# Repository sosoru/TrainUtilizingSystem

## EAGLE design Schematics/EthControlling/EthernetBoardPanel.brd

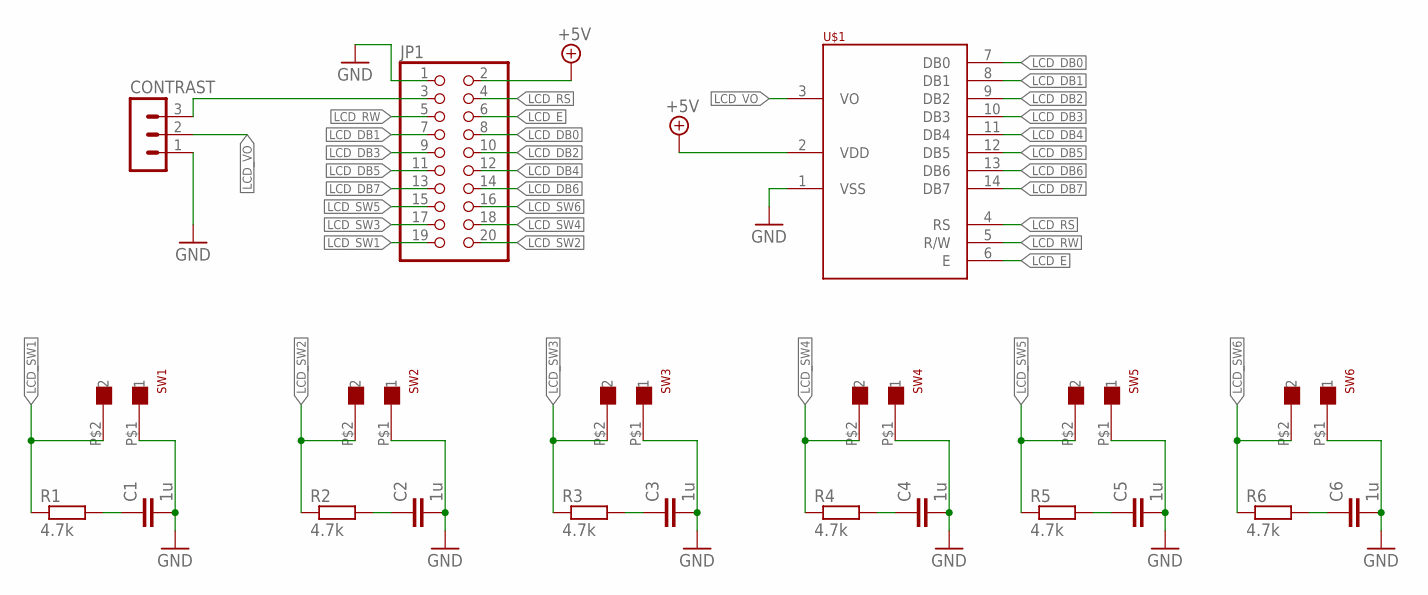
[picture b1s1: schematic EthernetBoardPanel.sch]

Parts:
C1, C2, C3, C4, C5, C6: 1u; C025-025X050
CONTRAST: MA03-1
JP1: PINHD-2X10; 2X10
R1, R2, R3, R4, R5, R6: 4.7k; 0204/7
SW1, SW2, SW3, SW4, SW5, SW6: XH-2
U$1: SC2004

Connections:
+5V: JP1.2, U$1.2 (VDD)
GND: C1.2, C2.2, C3.2, C4.2, C5.2, C6.2, CONTRAST.1, JP1.1, SW1.P$1 (1), SW2.P$1 (1), SW3.P$1 (1), SW4.P$1 (1), SW5.P$1 (1), SW6.P$1 (1), U$1.1 (VSS)
LCD_DB0: JP1.8, U$1.7 (DB0)
LCD_DB1: JP1.7, U$1.8 (DB1)
LCD_DB2: JP1.10, U$1.9 (DB2)
LCD_DB3: JP1.9, U$1.10 (DB3)
LCD_DB4: JP1.12, U$1.11 (DB4)
LCD_DB5: JP1.11, U$1.12 (DB5)
LCD_DB6: JP1.14, U$1.13 (DB6)
LCD_DB7: JP1.13, U$1.14 (DB7)
LCD_E: JP1.6, U$1.6 (E)
LCD_RS: JP1.4, U$1.4 (RS)
LCD_RW: JP1.5, U$1.5 (R/W)
LCD_SW1: JP1.19, R1.1, SW1.P$2 (2)
LCD_SW2: JP1.20, R2.1, SW2.P$2 (2)
LCD_SW3: JP1.17, R3.1, SW3.P$2 (2)
LCD_SW4: JP1.18, R4.1, SW4.P$2 (2)
LCD_SW5: JP1.15, R5.1, SW5.P$2 (2)
LCD_SW6: JP1.16, R6.1, SW6.P$2 (2)
LCD_VO: CONTRAST.2, U$1.3 (VO)
unnamed: CONTRAST.3, JP1.3
unnamed: C5.1, R5.2
unnamed: C2.1, R2.2
unnamed: C3.1, R3.2
unnamed: C4.1, R4.2
unnamed: C1.1, R1.2
unnamed: C6.1, R6.2

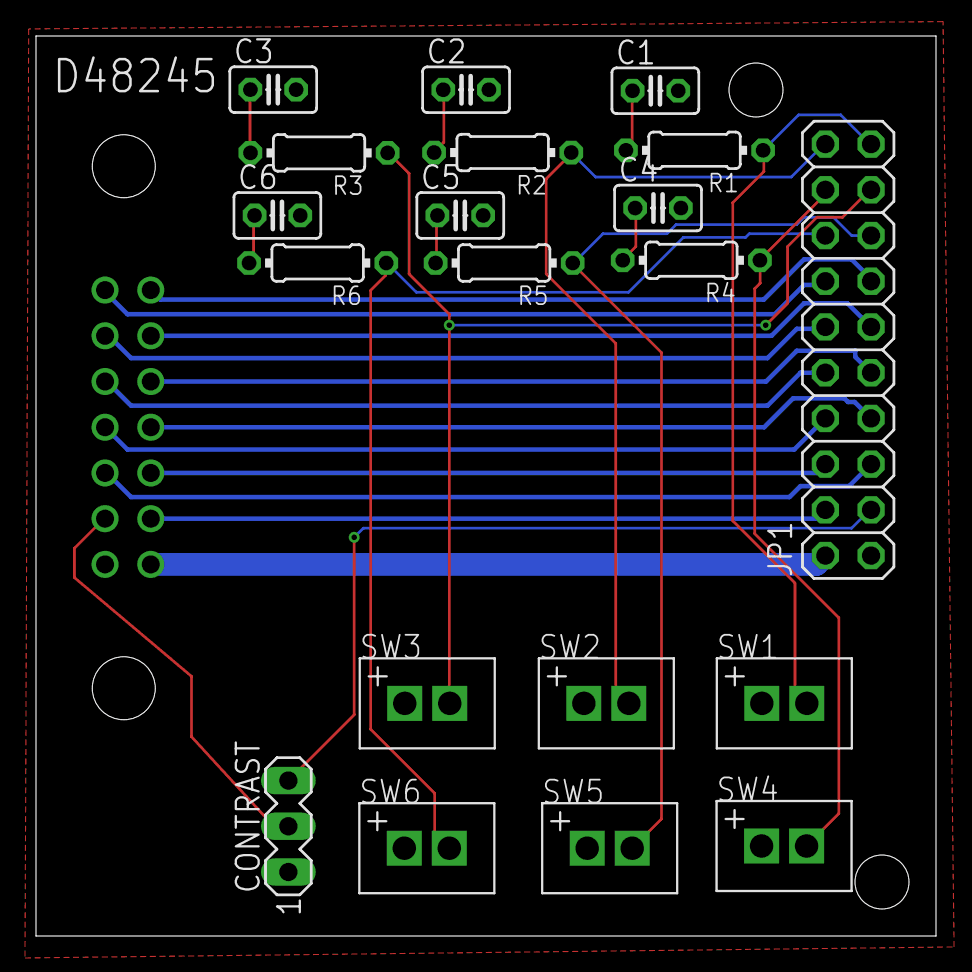
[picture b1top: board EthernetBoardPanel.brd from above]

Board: 2 copper layers, 50.0 x 50.0 mm, 21 parts (1 on the bottom side), 27 nets.

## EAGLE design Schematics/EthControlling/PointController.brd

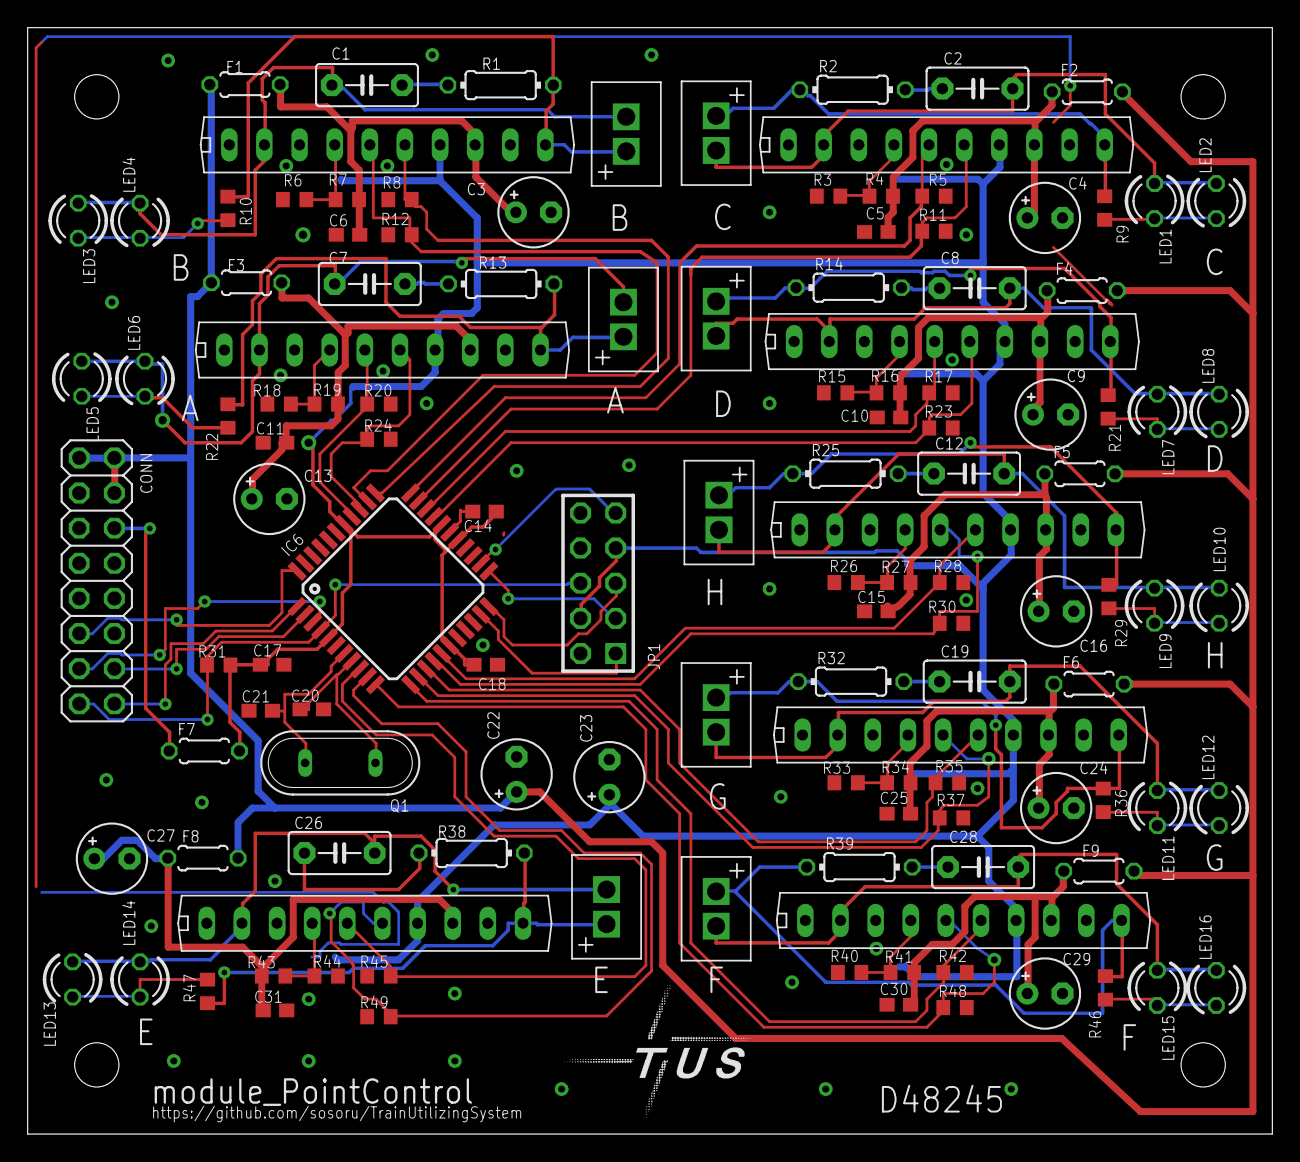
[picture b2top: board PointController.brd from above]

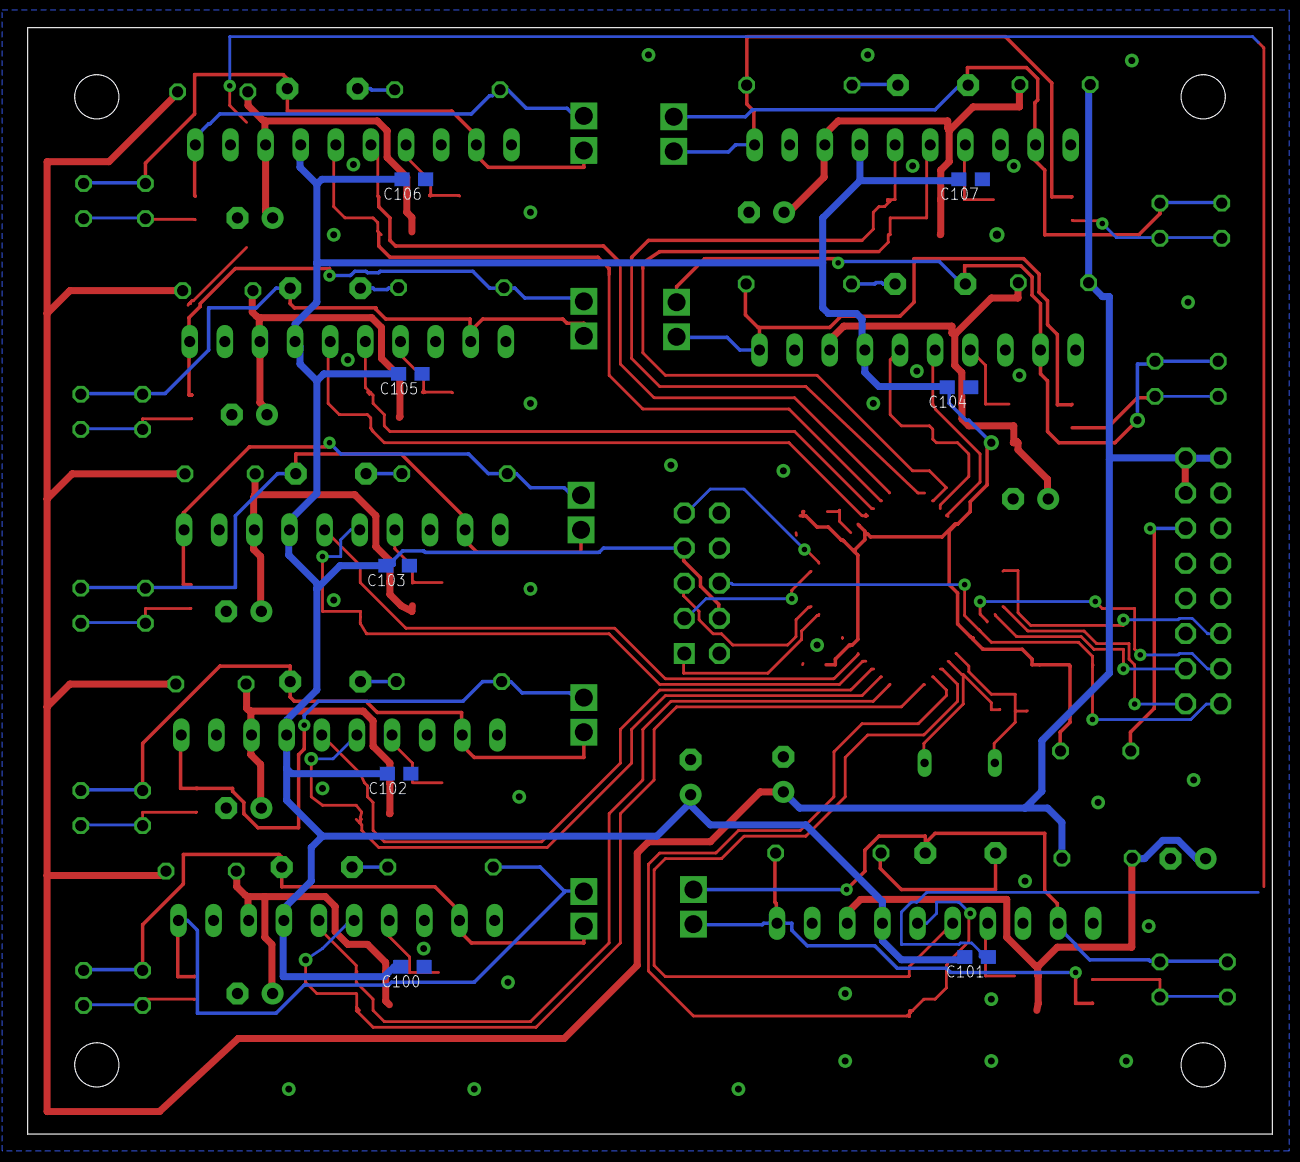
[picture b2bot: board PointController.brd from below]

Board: 2 copper layers, 90.0 x 80.0 mm, 133 parts (8 on the bottom side), 79 nets.

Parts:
A: XH-2
B: XH-2
C: XH-2
C1, C2, C7, C8, C12, C19, C26, C28: 47u; C5B3
C3, C4, C9, C13, C16, C24, C27, C29: E2,5-5
C5, C6, C10, C11, C14, C15, C17, C18, C25, C30, C31, C100, C101, C102, C103, C104, C105, C106, C107: 0.1u; C1608
C20, C21: 22p; C1608
C22, C23: 47u; E2,5-5
CONN: TUS_MODULE_SUPPLY; 2X08
D: XH-2
E: XH-2
F: XH-2
F1, F2, F3, F4, F5, F6, F7, F8, F9: POLYSWITCH_20204/5; 0204/5
G: XH-2
H: XH-2
IC1, IC2, IC3, IC4, IC5, IC7, IC8, IC9: TA7291; HSIP10
IC6: MEGA164P/324P/644P-AU; TQFP44
JP1: AVR-JTAG-10
LED1, LED3, LED5, LED7, LED9, LED11, LED13, LED15: G; LED3MM
LED2, LED4, LED6, LED8, LED10, LED12, LED14, LED16: O; LED3MM
Q1: 20.000M; QS
R1, R2, R13, R14, R25, R32, R38, R39: 10k; 0204/7
R3, R5, R6, R8, R11, R12, R15, R17, R18, R20, R23, R24, R26, R28, R30, R33, R35, R37, R40, R42, R44, R45, R48, R49: 100k; R0603
R4, R7, R16, R19, R27, R31, R34, R41, R43: 10k; R0603
R9, R10, R21, R22, R29, R36, R46, R47: 1k; R0603

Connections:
5V: C14.1, C17.1, C18.1, C23.+, C100.2, C101.2, C102.2, C103.2, C104.2, C105.2, C106.2, C107.2, F7.2, IC1.7, IC2.7, IC3.7, IC4.7, IC5.7, IC6.5, IC6.17, IC6.27, IC6.29, IC6.38, IC7.7, IC8.7, IC9.7, JP1.4, JP1.7, R31.1
!RESET: CONN.15, IC6.4, JP1.6, R31.2
!SS: CONN.11, IC6.44
+12V: C22.+, CONN.1, CONN.2, CONN.4, F1.2, F2.2, F3.2, F4.2, F5.2, F6.2, F8.2, F9.2
GND: C3.-, C4.-, C5.1, C6.1, C9.-, C10.1, C11.1, C13.-, C14.2, C15.1, C16.-, C17.2, C18.2, C20.1, C21.1, C22.-, C23.-, C24.-, C25.1, C27.-, C29.-, C30.1, C31.1, C100.1, C101.1, C102.1, C103.1, C104.1, C105.1, C106.1, C107.1, CONN.3, CONN.5, CONN.7, CONN.8, CONN.9, CONN.12, IC1.1, IC2.1, IC3.1, IC4.1, IC5.1, IC6.6, IC6.18, IC6.28, IC6.39, IC7.1, IC8.1, IC9.1, JP1.2, JP1.10, R3.2, R5.1, R6.2, R8.1, R11.1, R12.1, R15.2, R17.1, R18.2, R20.1, R23.1, R24.1, R26.2, R28.1, R30.1, R33.2, R35.1, R37.1, R40.2, R42.1, R44.2, R45.1, R48.1, R49.1
MISO: CONN.14, IC6.2
MOSI: CONN.16, IC6.1
unnamed: LED5.K, LED6.A, R22.2
unnamed: IC1.4, R6.1, R7.1
unnamed: C20.2, IC6.8, Q1.1
unnamed: C21.2, IC6.7, Q1.2
unnamed: B.P$2, C1.2, IC1.2, LED3.A, LED4.K
unnamed: IC4.4, R18.1, R19.1
unnamed: A.P$2, C7.2, IC4.2, LED5.A, LED6.K
unnamed: A.P$1, IC4.10, R13.1, R22.1
unnamed: C7.1, R13.2
unnamed: B.P$1, IC1.10, R1.1, R10.1
unnamed: C1.1, R1.2
unnamed: LED3.K, LED4.A, R10.2
unnamed: IC2.4, R3.1, R4.1
unnamed: C.P$2, C2.2, IC2.2, LED1.A, LED2.K
unnamed: C.P$1, IC2.10, R2.1, R9.1
unnamed: C2.1, R2.2
unnamed: LED1.K, LED2.A, R9.2
unnamed: IC3.4, R15.1, R16.1
unnamed: C8.2, D.P$2, IC3.2, LED7.A, LED8.K
unnamed: D.P$1, IC3.10, R14.1, R21.1
unnamed: C8.1, R14.2
unnamed: LED7.K, LED8.A, R21.2
unnamed: IC9.4, R43.1, R44.1
unnamed: C26.2, E.P$2, IC9.2, LED13.A, LED14.K
unnamed: E.P$1, IC9.10, R38.1, R47.1
unnamed: C26.1, R38.2
unnamed: LED13.K, LED14.A, R47.2
unnamed: IC8.4, R40.1, R41.1
unnamed: C28.2, F.P$2, IC8.2, LED15.A, LED16.K
unnamed: F.P$1, IC8.10, R39.1, R46.1
unnamed: C28.1, R39.2
unnamed: LED15.K, LED16.A, R46.2
unnamed: IC7.4, R33.1, R34.1
unnamed: C19.2, G.P$2, IC7.2, LED11.A, LED12.K
unnamed: G.P$1, IC7.10, R32.1, R36.1
unnamed: C19.1, R32.2
unnamed: LED11.K, LED12.A, R36.2
unnamed: IC5.4, R26.1, R27.1
unnamed: C12.2, H.P$2, IC5.2, LED9.A, LED10.K
unnamed: H.P$1, IC5.10, R25.1, R29.1
unnamed: C12.1, R25.2
unnamed: LED9.K, LED10.A, R29.2
unnamed: CONN.6, F7.1
unnamed: C11.2, C13.+, F3.1, IC4.8, R19.2
unnamed: C4.+, C5.2, F2.1, IC2.8, R4.2
unnamed: C27.+, C31.2, F8.1, IC9.8, R43.2
unnamed: C24.+, C25.2, F6.1, IC7.8, R34.2
unnamed: C15.2, C16.+, F5.1, IC5.8, R27.2
unnamed: C29.+, C30.2, F9.1, IC8.8, R41.2
unnamed: C9.+, C10.2, F4.1, IC3.8, R16.2
unnamed: C3.+, C6.2, F1.1, IC1.8, R7.2
OUT_A_0: IC4.5, IC6.37, R20.2
OUT_A_1: IC4.6, IC6.36, R24.2
OUT_B_0: IC1.5, IC6.35, R12.2
OUT_B_1: IC1.6, IC6.34, R8.2
OUT_C_0: IC2.5, IC6.33, R5.2
OUT_C_1: IC2.6, IC6.32, R11.2
OUT_D_0: IC3.5, IC6.31, R17.2
OUT_D_1: IC3.6, IC6.30, R23.2
OUT_E_0: IC6.9, IC9.5, R45.2
OUT_E_1: IC6.10, IC9.6, R49.2
OUT_F_0: IC6.11, IC8.5, R48.2
OUT_F_1: IC6.12, IC8.6, R42.2
OUT_G_0: IC6.13, IC7.5, R37.2
OUT_G_1: IC6.14, IC7.6, R35.2
OUT_H_0: IC5.5, IC6.15, R30.2
OUT_H_1: IC5.6, IC6.16, R28.2
SCK: CONN.13, IC6.3
TCK: IC6.21, JP1.1
TDI: IC6.24, JP1.9
TDO: IC6.23, JP1.3
TMS: IC6.22, JP1.5
